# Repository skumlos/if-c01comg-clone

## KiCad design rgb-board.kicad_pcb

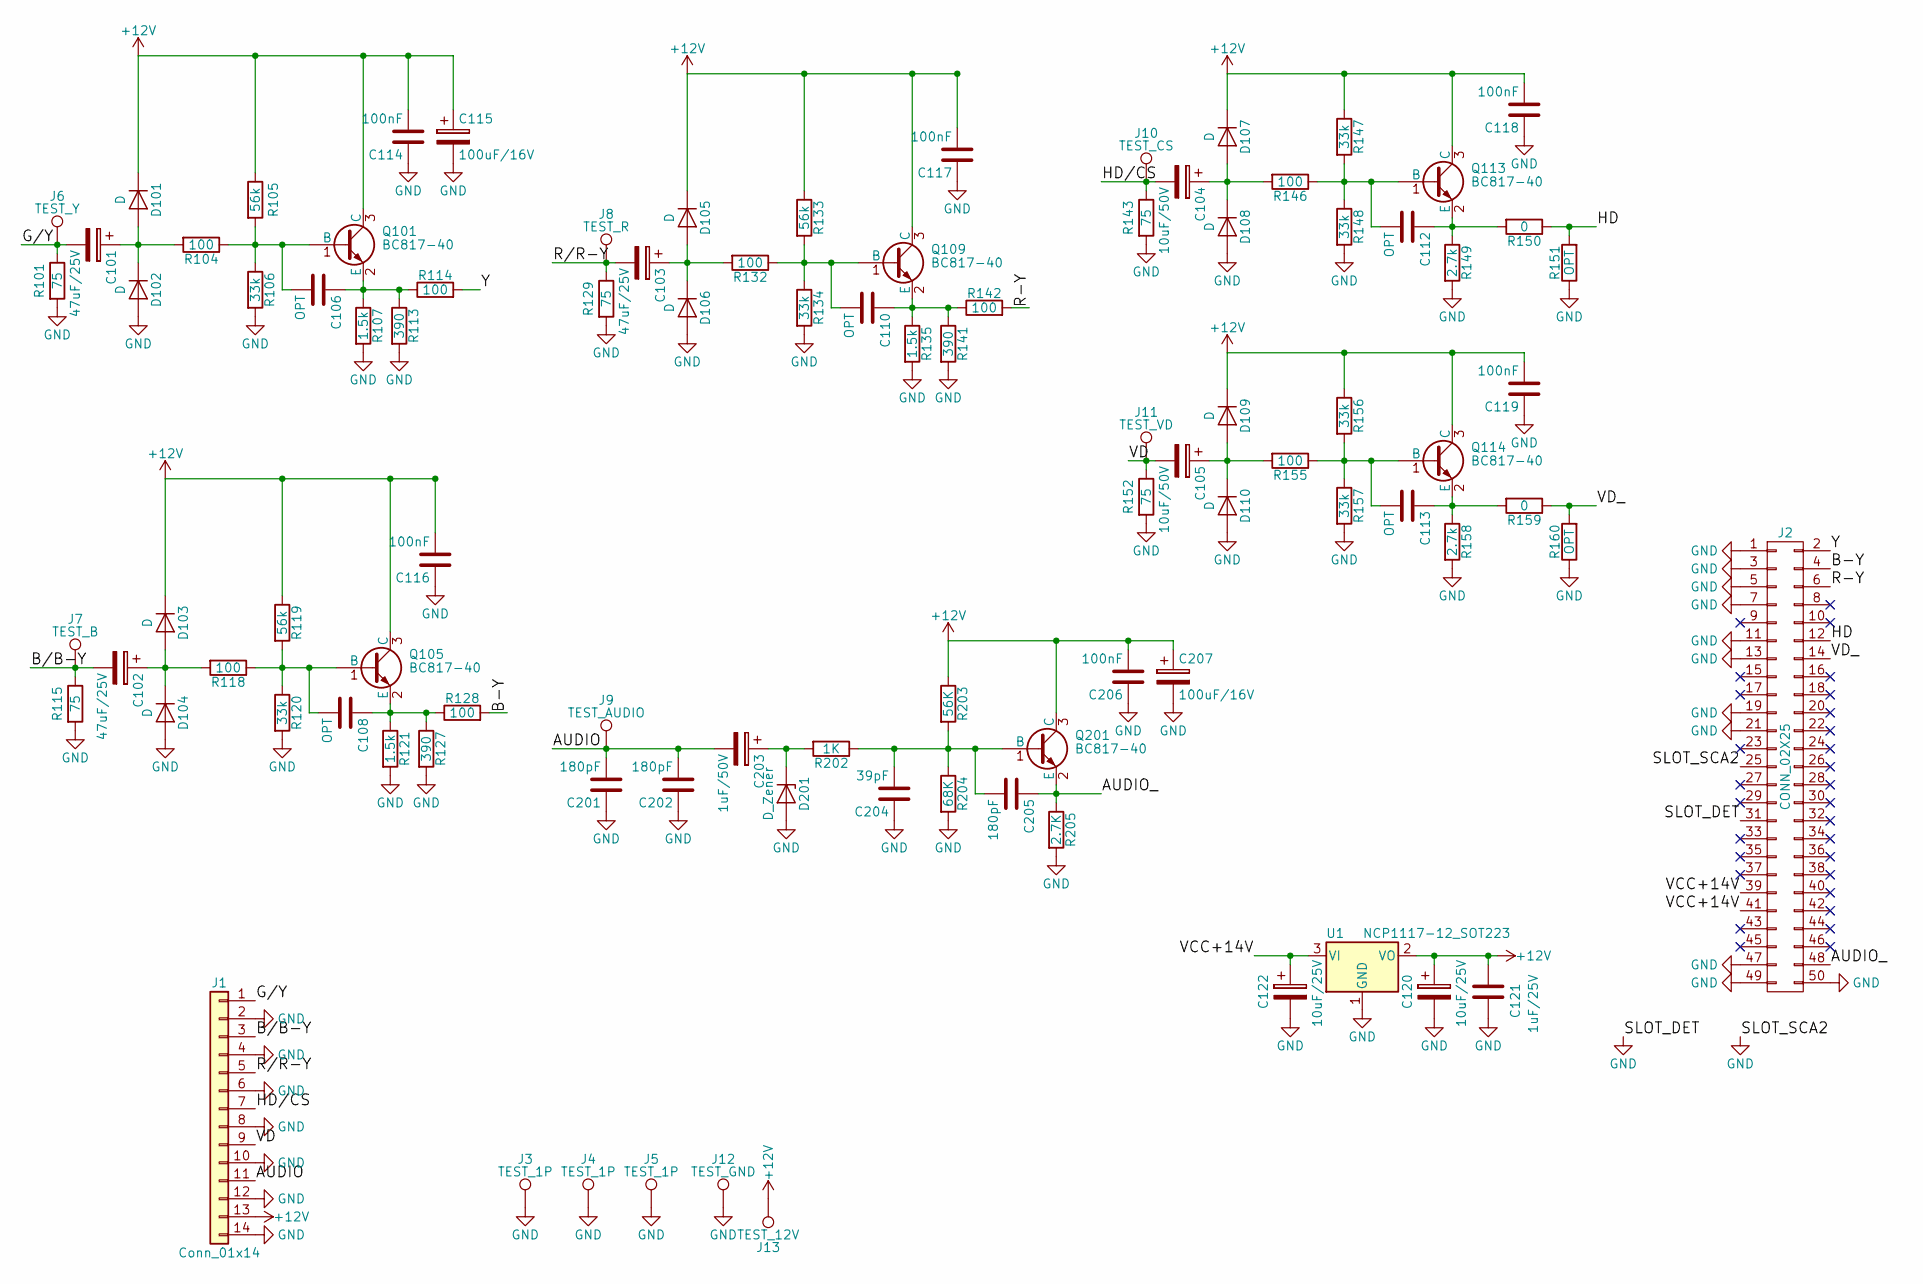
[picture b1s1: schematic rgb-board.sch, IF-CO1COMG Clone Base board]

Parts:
C101, C102, C103: 47uF/25V; CP_Elec_6.3x5.7
C104, C105: 10uF/50V; CP_Elec_5x5.7
C106, C108, C110, C112, C113: OPT; C_0805_HandSoldering
C114, C116, C117, C118, C119, C206: 100nF; C_0805_HandSoldering
C115, C207: 100uF/16V; CP_Elec_6.3x5.7
C120, C122: 10uF/25V; CP_Elec_5x5.7
C121: 1uF/25V; C_0805_HandSoldering
C201, C202, C205: 180pF; C_0805_HandSoldering
C203: 1uF/50V; CP_Elec_4x5.7
C204: 39pF; C_0805_HandSoldering
D101, D102, D103, D104, D105, D106, D107, D108, D109, D110: D; D_SOD-123
D201: D_Zener; D_SOD-123
J1: Conn_01x14; 52852-1472
J2: CONN_02X25; Pin_Header_Angled_2x25_Pitch2.54mm
J3, J4, J5: TEST_1P; MountingHole_3.2mm_M3
J6: TEST_Y; Measurement_Point_Round-SMD-Pad_Small
J7: TEST_B; Measurement_Point_Round-SMD-Pad_Small
J8: TEST_R; Measurement_Point_Round-SMD-Pad_Small
J9: TEST_AUDIO; Measurement_Point_Round-SMD-Pad_Small
J10: TEST_CS; Measurement_Point_Round-SMD-Pad_Small
J11: TEST_VD; Measurement_Point_Round-SMD-Pad_Small
J12: TEST_GND; Measurement_Point_Round-SMD-Pad_Small
J13: TEST_12V; Measurement_Point_Round-SMD-Pad_Small
Q101, Q105, Q109, Q113, Q114, Q201: BC817-40; SOT-23_Handsoldering
R101, R115, R129, R143, R152: 75; R_0805_HandSoldering
R104, R114, R118, R128, R132, R142, R146, R155: 100; R_0805_HandSoldering
R105, R119, R133: 56k; R_0805_HandSoldering
R106, R120, R134, R147, R148, R156, R157: 33k; R_0805_HandSoldering
R107, R121, R135: 1.5k; R_0805_HandSoldering
R113, R127, R141: 390; R_0805_HandSoldering
R149, R158: 2.7k; R_0805_HandSoldering
R150, R159: 0; R_0805_HandSoldering
R151, R160: OPT; R_0805_HandSoldering
R202: 1K; R_0805_HandSoldering
R203: 56K; R_0805_HandSoldering
R204: 68K; R_0805_HandSoldering
R205: 2.7K; R_0805_HandSoldering
U1: NCP1117-12_SOT223; TO-252-3_TabPin2

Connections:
+12V: C114.2, C115.1, C116.2, C117.2, C118.2, C119.2, C120.1, C121.2, C206.2, C207.1, D101.1 (K), D103.1 (K), D105.1 (K), D107.1 (K), D109.1 (K), J1.13, J13.1, Q101.3 (C), Q105.3 (C), Q109.3 (C), Q113.3 (C), Q114.3 (C), Q201.3 (C), R105.1, R119.1, R133.1, R147.1, R156.1, R203.1, U1.2 (VO)
/AUDIO: C201.2, C202.2, C203.2, J1.11, J9.1
/AUDIO_: C205.1, J2.48, Q201.2 (E), R205.1
/B-Y: J2.4, R128.2
/B/B-Y: C102.2, J1.3, J7.1, R115.1
/G/Y: C101.2, J1.1, J6.1, R101.1
/HD: J2.12, R150.1, R151.2
/HD/CS: C104.2, J1.7, J10.1, R143.1
/R-Y: J2.6, R142.2
/R/R-Y: C103.2, J1.5, J8.1, R129.1
/VCC+14V: C122.1, J2.39, J2.41, U1.3 (VI)
/VD: C105.2, J1.9, J11.1, R152.1
/VD_: J2.14, R159.1, R160.2
/Y: J2.2, R114.2
GND: C114.1, C115.2, C116.1, C117.1, C118.1, C119.1, C120.2, C121.1, C122.2, C201.1, C202.1, C204.1, C206.1, C207.2, D102.2 (A), D104.2 (A), D106.2 (A), D108.2 (A), D110.2 (A), D201.2 (A), J1.2, J1.4, J1.6, J1.8, J1.10, J1.12, J1.14, J2.1, J2.3, J2.5, J2.7, J2.11, J2.13, J2.19, J2.21, J2.25, J2.31, J2.47, J2.49, J2.50, J3.1, J4.1, J5.1, J12.1, R101.2, R106.2, R107.2, R113.2, R115.2, R120.2, R121.2, R127.2, R129.2, R134.2, R135.2, R141.2, R143.2, R148.2, R149.2, R151.1, R152.2, R157.2, R158.2, R160.1, R204.2, R205.2, U1.1 (GND)
unnamed: C101.1, D101.2 (A), D102.1 (K), R104.2
unnamed: C102.1, D103.2 (A), D104.1 (K), R118.2
unnamed: C103.1, D105.2 (A), D106.1 (K), R132.2
unnamed: C104.1, D107.2 (A), D108.1 (K), R146.2
unnamed: C105.1, D109.2 (A), D110.1 (K), R155.2
unnamed: C106.1, Q101.2 (E), R107.1, R113.1, R114.1
unnamed: C106.2, Q101.1 (B), R104.1, R105.2, R106.1
unnamed: C108.1, Q105.2 (E), R121.1, R127.1, R128.1
unnamed: C108.2, Q105.1 (B), R118.1, R119.2, R120.1
unnamed: C110.1, Q109.2 (E), R135.1, R141.1, R142.1
unnamed: C110.2, Q109.1 (B), R132.1, R133.2, R134.1
unnamed: C112.1, Q113.2 (E), R149.1, R150.2
unnamed: C112.2, Q113.1 (B), R146.1, R147.2, R148.1
unnamed: C113.1, Q114.2 (E), R158.1, R159.2
unnamed: C113.2, Q114.1 (B), R155.1, R156.2, R157.1
unnamed: C203.1, D201.1 (K), R202.2
unnamed: C204.2, C205.2, Q201.1 (B), R202.1, R203.2, R204.1

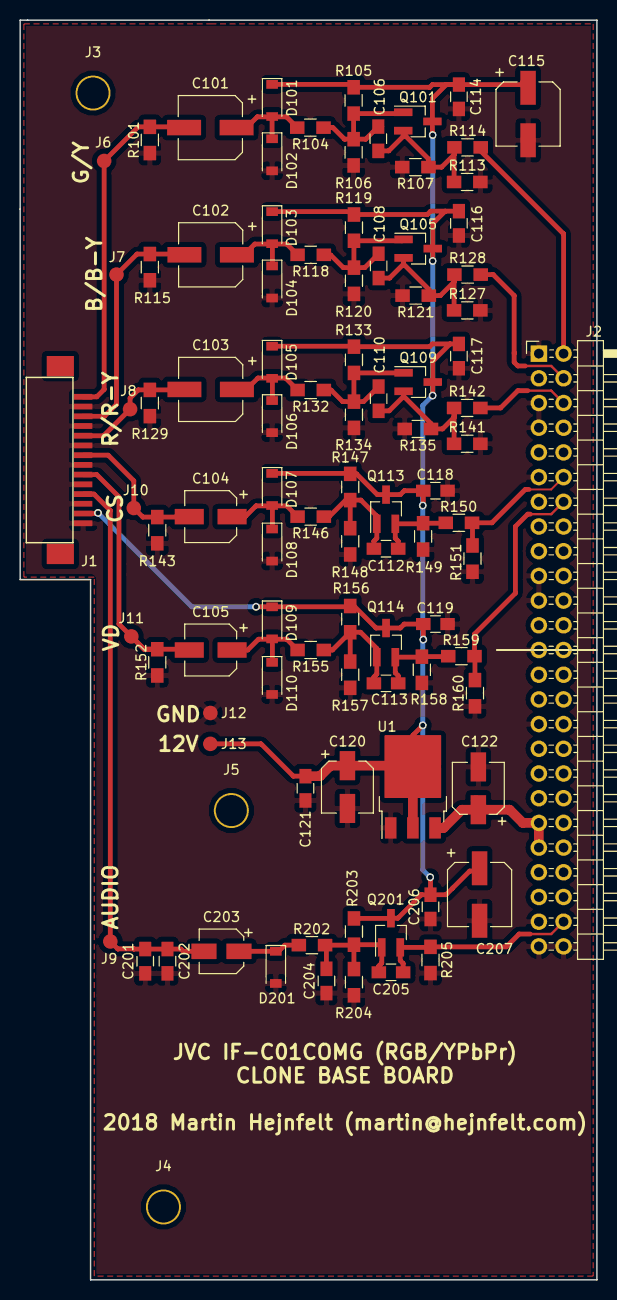
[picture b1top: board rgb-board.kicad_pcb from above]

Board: 2 copper layers, 59.3 x 129.5 mm, 96 parts (0 on the bottom side), 32 nets.
